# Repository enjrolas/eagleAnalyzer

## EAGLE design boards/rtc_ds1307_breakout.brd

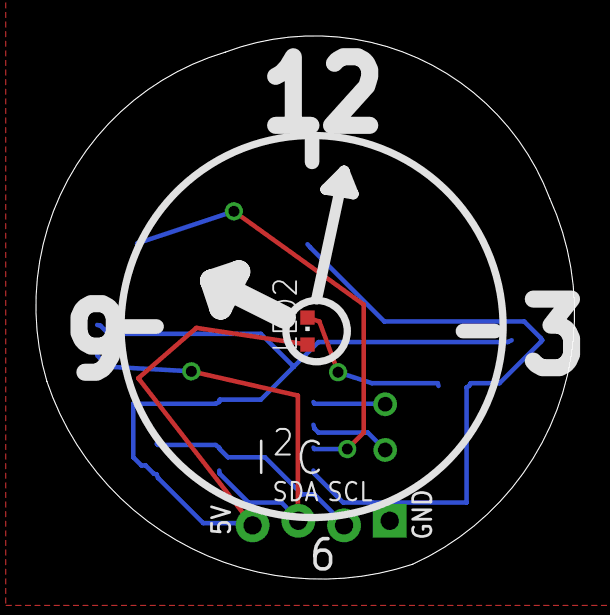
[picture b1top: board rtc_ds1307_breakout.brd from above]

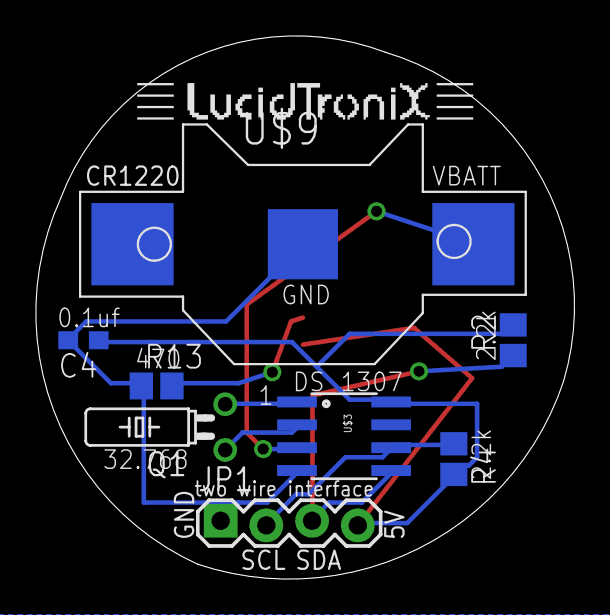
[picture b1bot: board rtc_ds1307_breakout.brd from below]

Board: 2 copper layers, 29.9 x 30.2 mm, 10 parts (9 on the bottom side), 8 nets.

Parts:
C4: 0.1uf; C0603
JP1: 1X04_LOCK
LED2: CHIPLED_0603
Q1: 32.768; TC26H
R2, R4: 2.2k; R0805
R13: 300; R0805
U$1: LUCIDTRONIX_LOGO_.75_INCH
U$3: DS1307SO8; SO08
U$9: CR1220-SMD

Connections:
+5V: C4.1, JP1.4, LED2.A, R2.2, R4.2, U$3.8
GND: C4.2, JP1.1, R13.1, U$3.4, U$9.-
unnamed: Q1.1, U$3.2
unnamed: U$3.3, U$9.+$2
unnamed: Q1.2, U$3.1
unnamed: LED2.C, R13.2
SCL: JP1.2, R4.1, U$3.6
SDA: JP1.3, R2.1, U$3.5

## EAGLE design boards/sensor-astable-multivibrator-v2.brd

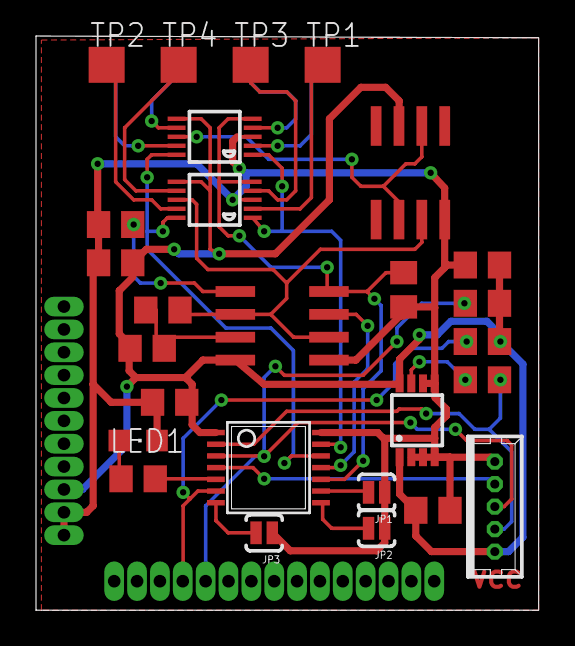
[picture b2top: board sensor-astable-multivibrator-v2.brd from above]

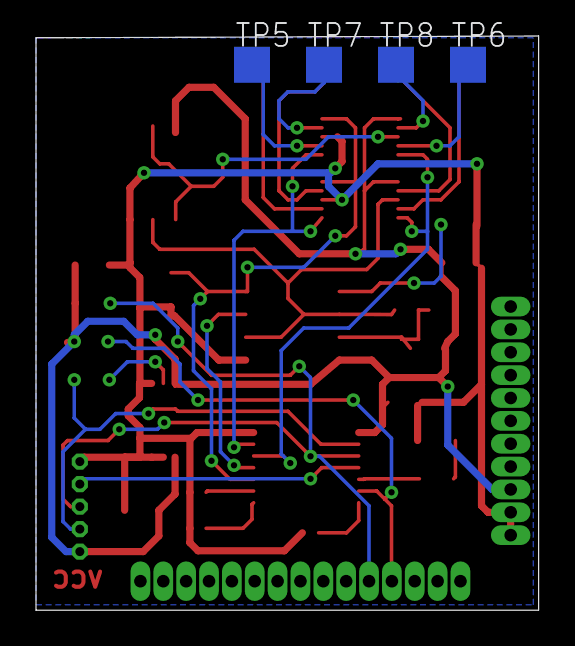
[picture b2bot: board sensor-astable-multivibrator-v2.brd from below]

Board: 2 copper layers, 27.9 x 31.9 mm, 32 parts (4 on the bottom side), 28 nets.

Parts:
C1: 100n; C0805
C3, C4, C5: 0,1µF; C0805
CT: 10u; C0805
IC1: TLC555; SO08
JP1, JP2, JP3: SJ_2S-NO
LED1: CHIPLED_0805
R1, R4, R5: 10k; R0805
R6: 22; R0805
R9: 27; R0805
RA: 100k; R0805
RB: 1k; R0805
THS4281: THS4281; SO08
TP1, TP2, TP3, TP4, TP5, TP6, TP7, TP8: TPTP20SQ; TP20SQ
U$1: CAPSENSE-BREAKOUT-I2C; JENNIC-FOOTPRINT-RB
U$2, U$5: ADG704; MSOP10
U$3: LTC6930-X.XX; MSOP8
U$4: ATTINY20; TSSOP14
X2: PROGCON; 53047-05-OCT

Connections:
(TPI)CLK: R6.2, U$4.2, X2.2
/RESET: U$4.4, X2.4
A0: U$2.1, U$4.13, U$5.1
A1: U$2.10, U$4.12, U$5.10
ADDR0: JP1.2, U$4.9
ADDR1: JP2.2, U$4.8
ADDR2: JP3.2, U$4.7
ANTENNA: IC1.2, IC1.6, RA.2, THS4281.3, U$2.8
BLUE: R9.1, U$4.5
ENABLE: IC1.4, R1.2, U$2.5, U$4.10, U$5.5
GND: C1.2, C3.2, C4.2, C5.2, CT.2, IC1.1, JP1.1, JP2.1, JP3.1, LED1.C, R1.1, THS4281.4, U$1.P$25, U$1.P$26, U$2.3, U$3.2, U$3.3, U$3.4, U$3.5, U$3.6, U$4.14, U$5.3, X2.5
GUARD: THS4281.2, THS4281.6, U$5.8
unnamed: IC1.7, RA.1, RB.2
unnamed: TP1.TP, U$2.2
unnamed: C1.1, IC1.5
unnamed: TP2.TP, U$2.9
unnamed: TP3.TP, U$2.4
unnamed: TP4.TP, U$2.7
unnamed: TP5.TP, U$5.2
unnamed: TP6.TP, U$5.9
unnamed: TP7.TP, U$5.4
unnamed: TP8.TP, U$5.7
unnamed: R6.1, U$3.7
unnamed: LED1.A, R9.2
OUT: IC1.3, U$4.11
SCL: R5.1, U$1.P$30, U$4.6
SDA/TPIDATA: R4.1, U$1.P$31, U$4.3, X2.3
VCC: C3.1, C4.1, C5.1, CT.1, IC1.8, R4.2, R5.2, RB.1, THS4281.7, U$1.P$24, U$2.6, U$3.1, U$3.8, U$4.1, U$5.6, X2.1

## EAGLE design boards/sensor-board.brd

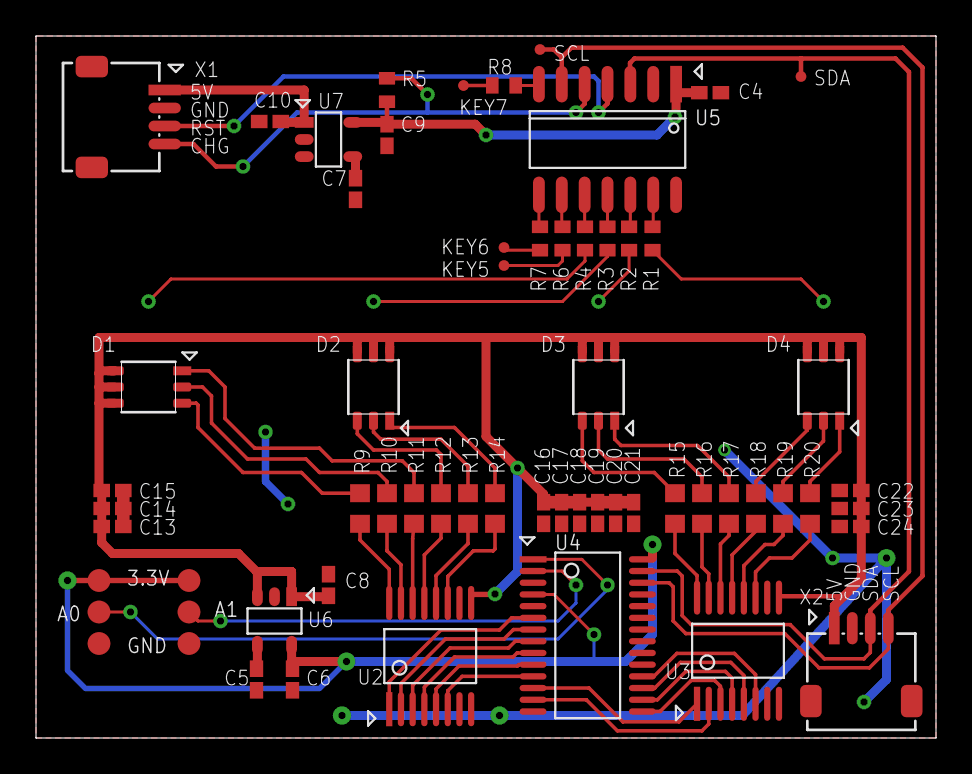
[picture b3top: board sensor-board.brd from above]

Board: 2 copper layers, 50.0 x 39.0 mm, 62 parts (0 on the bottom side), 59 nets.

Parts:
3.3V: TPB1,27; B1,27
A0, A1: TPB1,27; B1,27
C4: 0.1uF 100V; C0402K
C5, C7, C13: 0.01uF 25V; C0402K
C6, C9: 2.2uF 10V; C0402K
C8, C10: 1uF 25V; C0402K
C14, C15, C16, C17, C18, C19, C20, C21, C22, C23, C24: 0.01uF 16V; C0402K
D1, D2, D3, D4: ASMT-YTC2-0AA02; ASMT-YTC2-0AA02-REV
GND: TPB1,27; B1,27
KEY5, KEY6, KEY7: TPTP06R; TP06R
R1, R2, R3, R4, R6, R7, R8: 4.7k; R0402
R5: 47k; R0402
R9, R10, R11, R12, R13, R14, R15, R16, R17, R18, R19, R20: 60R 145mW; R0603
SCL: TPTP06R; TP06R
SDA: TPTP06R; TP06R
TP1, TP3: TPB1,27; B1,27
U2, U3: ULN2003LVPWR; TSSOP-PW-R-PDSO-G16
U4: PCA9685PW; SOT361-1
U5: AT42QT1070-SSU; SO14
U6, U7: TPS730XX; SOT23-5
X1, X2: MOLEX-501953-0407

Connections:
!CAPSENSE_CHG!: R5.1, U5.5, X1.4
!CAPSENSE_RST!: U5.4, X1.3
GND: C4.2, C5.2, C6.1, C7.2, C8.2, C9.2, C10.1, C13.1, C14.1, C15.1, C16.1, C17.1, C18.1, C19.1, C20.1, C21.1, C22.1, C23.1, C24.1, GND.TP, TP3.TP, U2.7, U2.8, U3.7, U3.8, U4.3, U4.5, U4.14, U4.23, U4.24, U4.25, U5.2, U5.14, U6.2, U7.2, X1.2, X1.5, X1.6, X2.2, X2.5, X2.6
KEY5: KEY5.TP, R6.2
KEY6: KEY6.TP, R7.2
KEY7: KEY7.TP, R8.2
LEDOUT_A1: U2.1, U4.6
LEDOUT_A2: U2.2, U4.7
LEDOUT_A3: U2.3, U4.8
LEDOUT_A4: U2.4, U4.9
LEDOUT_A5: U2.5, U4.10
LEDOUT_A6: U2.6, U4.11
LEDOUT_B1: U3.1, U4.12
LEDOUT_B2: U3.2, U4.13
LEDOUT_B3: U3.3, U4.15
LEDOUT_B4: U3.4, U4.16
LEDOUT_B5: U3.5, U4.17
LEDOUT_B6: U3.6, U4.18
unnamed: C5.1, U6.4
unnamed: A0.TP, U4.1
unnamed: A1.TP, U4.2
unnamed: C7.1, U7.4
unnamed: R6.1, U5.9
unnamed: R7.1, U5.8
unnamed: R8.1, U5.7
unnamed: R1.1, U5.13
unnamed: R2.1, U5.12
unnamed: R3.1, U5.11
unnamed: R4.1, U5.10
unnamed: D4.1, R20.2
unnamed: D1.1, R11.2
unnamed: D1.2, R10.2
unnamed: D3.3, R15.2
unnamed: D2.3, R12.2
unnamed: D2.2, R13.2
unnamed: R15.1, U3.16
unnamed: R16.1, U3.15
unnamed: D3.1, R17.2
unnamed: D3.2, R16.2
unnamed: D4.3, R18.2
unnamed: D4.2, R19.2
unnamed: R17.1, U3.14
unnamed: R18.1, U3.13
unnamed: R19.1, U3.12
unnamed: R20.1, U3.11
unnamed: D2.1, R14.2
unnamed: D1.3, R9.2
unnamed: R9.1, U2.16
unnamed: R10.1, U2.15
unnamed: R11.1, U2.14
unnamed: R12.1, U2.13
unnamed: R13.1, U2.12
unnamed: R14.1, U2.11
SCL: SCL.TP, U4.26, U5.6, X2.4
SDA: SDA.TP, U4.27, U5.3, X2.3
VDD_3_3_CAPSENSE: C4.1, C9.1, R5.2, U5.1, U7.5
VDD_3_3_PWMDRIVE: 3.3V.TP, C6.2, TP1.TP, U4.4, U4.28, U6.5
VDD_5_CAPSENSE: C10.2, U7.1, U7.3, X1.1
VDD_5_ILLUM: C8.1, C13.2, C14.2, C15.2, C16.2, C17.2, C18.2, C19.2, C20.2, C21.2, C22.2, C23.2, C24.2, D1.4, D1.5, D1.6, D2.4, D2.5, D2.6, D3.4, D3.5, D3.6, D4.4, D4.5, D4.6, U2.9, U3.9, U6.1, U6.3, X2.1

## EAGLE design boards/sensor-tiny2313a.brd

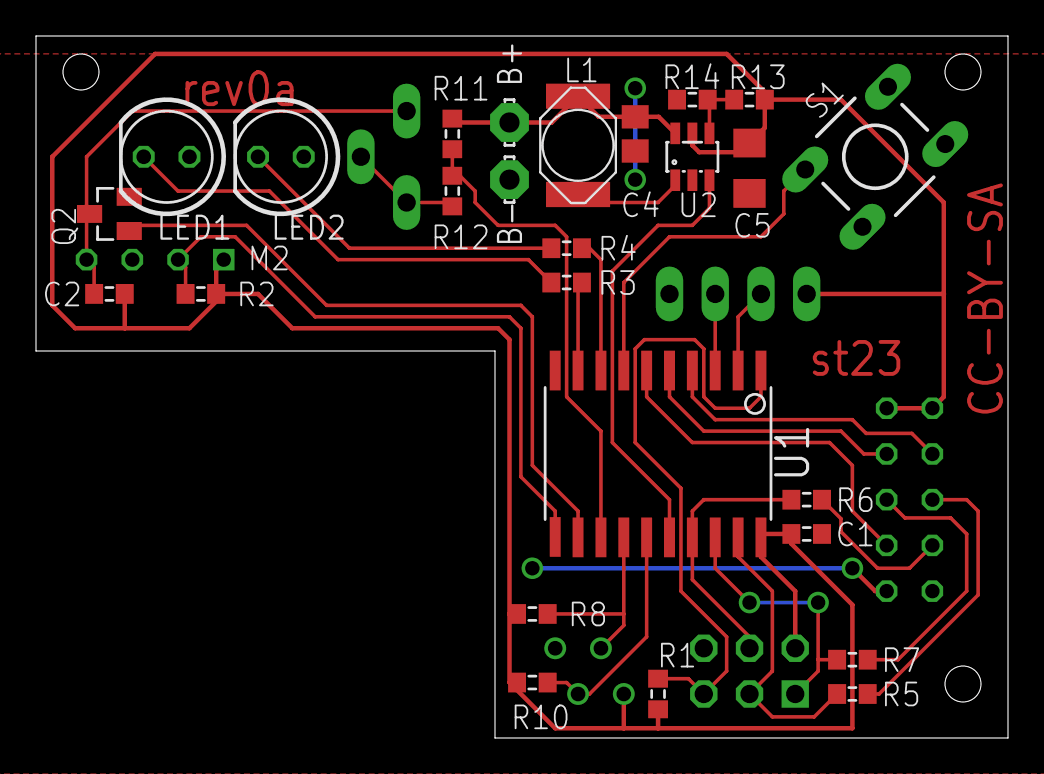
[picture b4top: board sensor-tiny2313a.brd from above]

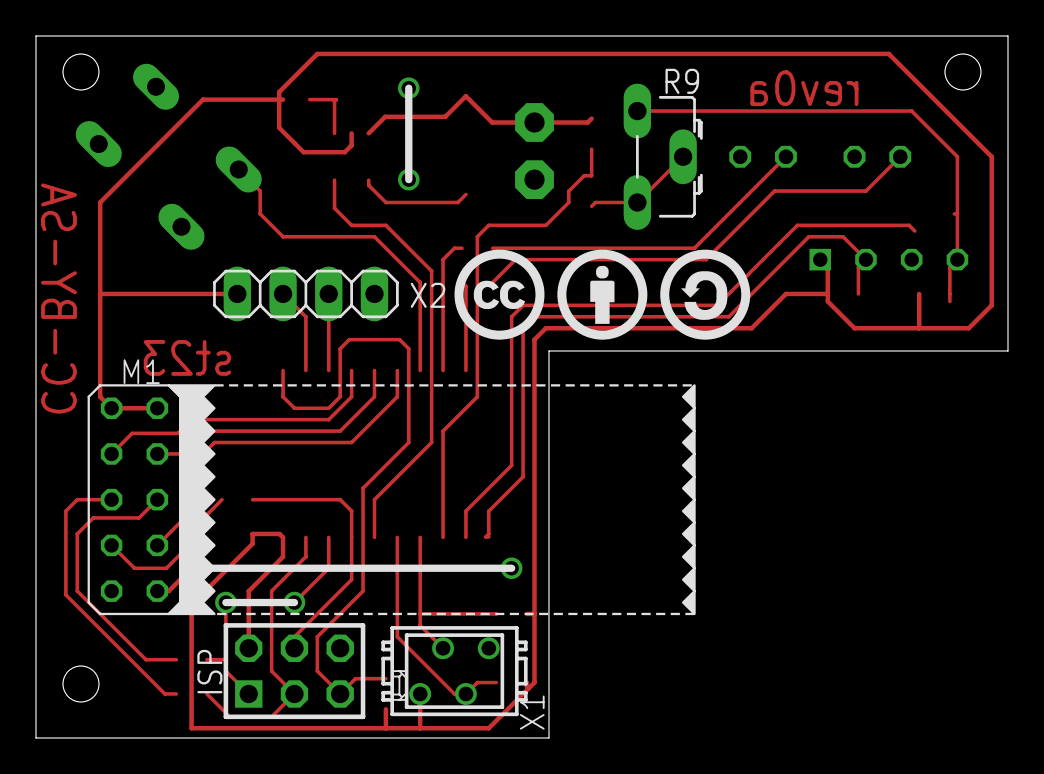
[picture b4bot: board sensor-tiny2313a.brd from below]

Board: 2 copper layers, 54.0 x 39.0 mm, 36 parts (8 on the bottom side), 30 nets.

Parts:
B+: LSP11
B-: LSP11
C1, C2: 100n; C0603
C4: 4u7; C0805
C5: 22u; C1206
ISP: ML6; AVR-ISP-6
L1: 4u7; PISG
LED1: GR LC; LED5MM
LED2: RT LC; LED5MM
M1: NRF24L01P-M; NRF24L01P-A
M2: DHT22-NP; DHT22-NOPRINT
Q2: IRLML2502; MICRO3
R1, R2, R11: 10k; R0603
R3: 470; R0603
R4: 510; R0603
R5, R6, R7, R8, R10: 4k7; R0603
R9: 2k5; CA6H
R12: 12k; R0603
R13: 470k; R0603
R14: 270k; R0603
S1: DTS-6
U1: TINY2313-*S*; SO20L$
U2: MCP1640C; SOT23-6
U$1: CC-TPLACE-HALF; CC_TPLACE_HS
U$2: SP6029TOP; SP6029T
U$3: BY-TPLACE-HS; BY_TPLACE_HS
U$4: SA-TPLACE-HALF; SA_TPLACE_HS
X1: I2C; MICROMATCH-4
X2: serial; 1X04

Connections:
!RESET: ISP.5, R1.2, U1.1
AIN1: R11.2, R12.1, U1.13
DHTON: Q2.1, U1.12
DI: ISP.4, R6.1, U1.17
DO: ISP.1, R7.2, U1.18
GND: B-.MP, C1.2, C4.2, C5.2, ISP.6, LED1.A, LED2.A, M1.GND_A, M1.GND_B, Q2.2, R14.1, S1.3, S1.4, U1.10, U2.2, X1.4, X2.4
ICP1: M2.2, R2.2, U1.11
LED1: R3.1, U1.9
LED2: R4.1, U1.8
unnamed: LED2.K, R4.2
unnamed: C2.1, M2.4, Q2.3, R9.A
unnamed: LED1.K, R3.2
unnamed: R9.E, R9.S, R12.2
unnamed: L1.1, U2.1
unnamed: R13.2, R14.2, U2.4
PWRON: U1.16, U2.3
RDI: M1.MISO, R6.2
RDO: M1.MOSI, R7.1
RFCE: M1.CE, U1.4
RFCSN: M1.CSN, U1.5
RFIRQ: M1.IRQ, U1.6
RSCK: M1.SCK, R5.2
RXD: U1.2, X2.2
SCK: ISP.3, R5.1, U1.19
SCL: R10.2, U1.15, X1.3
SDA: R8.2, U1.14, X1.2
SW1: S1.1, U1.7
TXD: U1.3, X2.3
VBAT: B+.MP, C4.1, L1.2, R11.1, U2.6
VCC: C1.1, C2.2, C5.1, ISP.2, M1.VCC_A, M1.VCC_B, M2.1, R1.1, R2.1, R8.1, R10.1, R13.1, U1.20, U2.5, X1.1, X2.1

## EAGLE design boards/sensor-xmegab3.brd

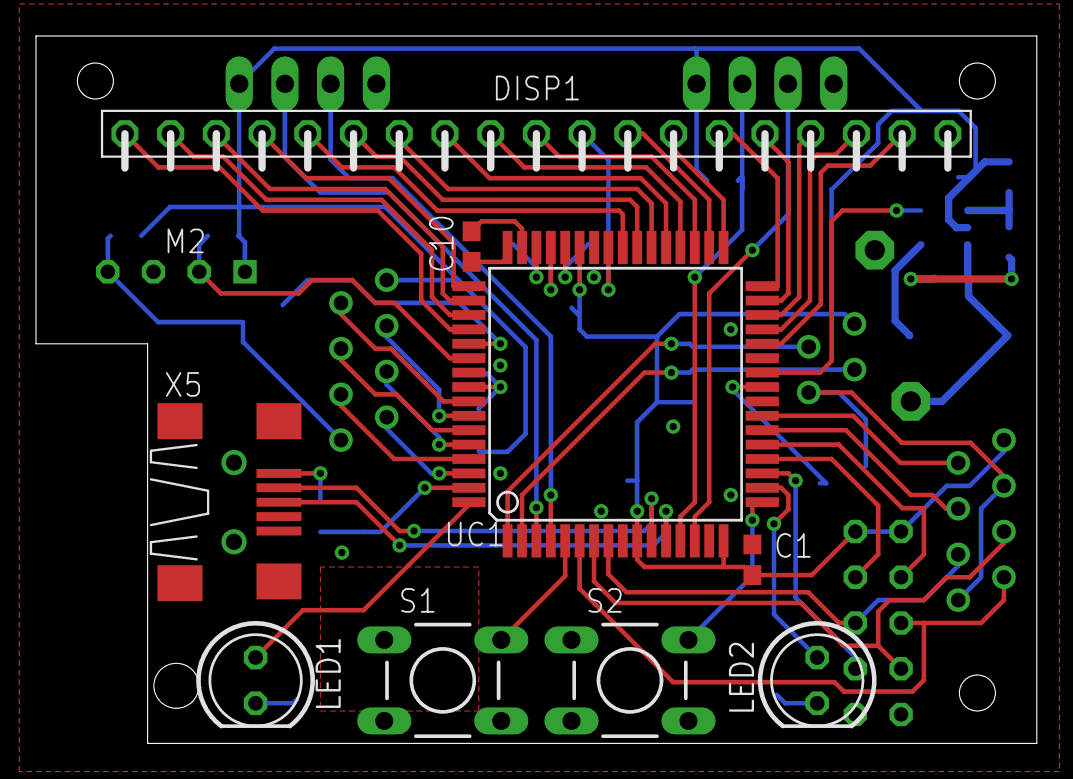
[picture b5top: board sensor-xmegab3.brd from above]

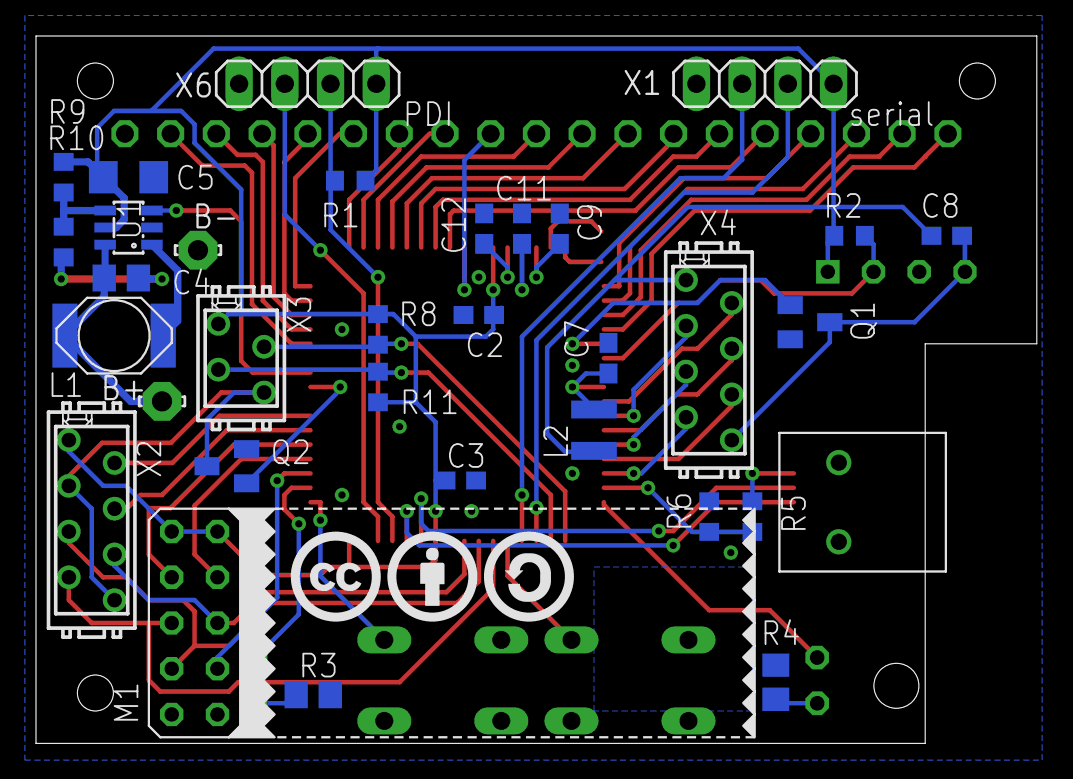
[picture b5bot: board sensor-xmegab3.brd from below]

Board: 2 copper layers, 55.6 x 39.3 mm, 46 parts (35 on the bottom side), 65 nets.

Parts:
B+: LSP11
B-: LSP11
C1, C2, C3, C7, C8, C9, C10, C11, C12: 100n; C0603
C4: 4u7; C0805
C5: 22u; C1206
DISP1: DE325
K1: SP6029TOP; SP6029T
L1: 4u7; PISG
L2: 10u; SM-NE29
LED1: GR LC; LED5MM
LED2: RT LC; LED5MM
M1: NRF24L01P-M; NRF24L01P-A
M2: DHT22-NP; DHT22-NOPRINT
Q1, Q2: IRLML2502; MICRO3
R1, R2, R6: 10k; R0603
R3: 510; R0805
R4: 470; R0805
R5: 15k; R0603
R8, R11: 4k7; R0603
R9: 470k; R0603
R10: 270k; R0603
S1, S2: DTS-6
U1: MCP1640C; SOT23-6
U$1: CC-TPLACE-HALF; CC_TPLACE_HS
U$3: BY-TPLACE-HS; BY_TPLACE_HS
U$4: SA-TPLACE-HALF; SA_TPLACE_HS
UC1: XMEGA-B3; TQFP64
X1: serial; 1X04
X2: SPI/1W; MICROMATCH-8
X3: I2C; MICROMATCH-4
X4: ADC; MICROMATCH-8
X5: USB-MB-S
X6: PDI; 1X04

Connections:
ADC0: UC1.57, X4.2
ADC1: UC1.58, X4.3
ADC2: UC1.59, X4.4
ADC3: UC1.60, X4.5
ADC4: UC1.61, X4.6
ADC5: UC1.62, X4.7
AVCC: C7.1, L2.2, UC1.56
COM0: DISP1.4, UC1.49
COM1: DISP1.3, UC1.50
COM2: DISP1.2, UC1.51
COM3: DISP1.1, UC1.52
DHTADCON: Q1.1, UC1.53
GND: B-.MP, C1.2, C2.2, C3.2, C4.2, C5.2, C7.2, C9.1, C11.1, C12.1, M1.GND_A, M1.GND_B, Q1.2, Q2.2, R3.2, R4.2, R6.1, R10.1, S1.3, S1.4, S2.3, S2.4, U1.2, UC1.9, UC1.15, UC1.42, UC1.55, X1.4, X5.GND, X6.4
ICP: M2.2, R2.1, UC1.54
LED1: LED1.A, UC1.64
LED2: LED2.A, UC1.18
MISO: M1.MISO, UC1.7, X2.5
MOSI: M1.MOSI, UC1.8, X2.6
unnamed: LED1.K, R4.1
unnamed: R5.1, X5.VBUS
unnamed: LED2.K, R3.1
unnamed: L1.1, U1.1
unnamed: R9.2, R10.2, U1.4
unnamed: C11.2, UC1.45
unnamed: C12.2, UC1.44
unnamed: Q2.3, X2.3, X2.8, X3.4
unnamed: C8.1, M2.4, Q1.3, X4.8
unnamed: C9.2, UC1.46
unnamed: C10.1, UC1.47
unnamed: C10.2, UC1.48
PDIC: R1.2, UC1.13, X6.2
PDID: UC1.14, X6.3
PWRON: U1.3, UC1.26
RFCE: M1.CE, UC1.21
RFCSN: M1.CSN, UC1.20
RFIRQ: M1.IRQ, UC1.19
RXD: UC1.3, X1.2
SCK: M1.SCK, UC1.6, X2.7
SCL: R11.2, UC1.2, X3.3
SDA: R8.2, UC1.1, X3.2
SEG0: DISP1.5, UC1.40
SEG1: DISP1.6, UC1.39
SEG2: DISP1.7, UC1.38
SEG3: DISP1.8, UC1.37
SEG4: DISP1.9, UC1.36
SEG5: DISP1.10, UC1.35
SEG6: DISP1.11, UC1.41
SEG7: DISP1.12, UC1.34
SEG8: DISP1.13, UC1.33
SEG9: DISP1.14, UC1.32
SEG10: DISP1.15, UC1.31
SEG11: DISP1.16, UC1.30
SEG12: DISP1.17, UC1.29
SEG13: DISP1.18, UC1.28
SPI1WON: Q2.1, UC1.25
SS1WA: UC1.22, X2.4
SS1WB: UC1.23, X2.2
SW1: S1.2, UC1.5
SW2: S2.2, UC1.17
TXD: UC1.4, X1.3
USBD_N: UC1.11, X5.D-
USBD_P: UC1.12, X5.D+
USBV: R5.2, R6.2, UC1.63
VBAT: B+.MP, C4.1, L1.2, U1.6
VCC: C1.1, C2.1, C3.1, C5.1, C8.2, L2.1, M1.VCC_A, M1.VCC_B, M2.1, R1.1, R2.2, R8.1, R9.1, R11.1, U1.5, UC1.10, UC1.16, UC1.43, X1.1, X2.1, X3.1, X4.1, X6.1

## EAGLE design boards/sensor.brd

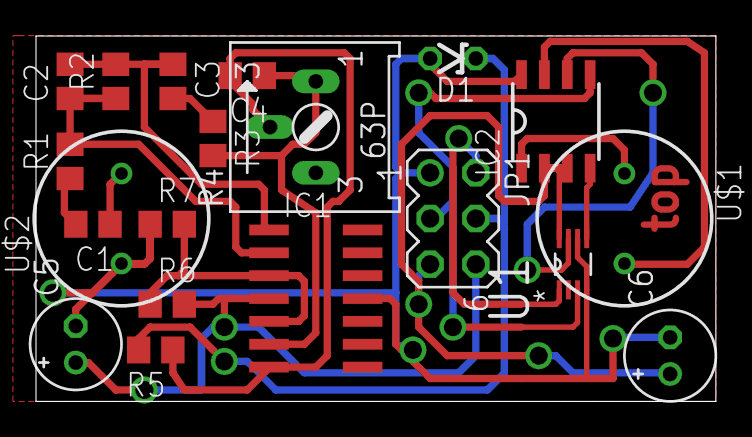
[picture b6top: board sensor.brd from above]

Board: 2 copper layers, 37.8 x 20.3 mm, 20 parts (0 on the bottom side), 18 nets.

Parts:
C1: 100n; C0805
C2, C3, C4: C0805
C5, C6: 10uF; E2-5
D1: 3V3; ZDIO-2.5
IC1: LM324D; SO14
IC2: BD6211F; SOP8
JP1: MA03-2
R1, R3: 1K5; R0805
R2: 5K6; R0805
R4: 100K; S63P
R5: 100; R0805
R6: 1K; R0805
R7: 470; R0805
U1: NC7NZ04K8X; SOP50P310X90-8N
U$1, U$2: TRANSDUCER

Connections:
GND: C5.-, C6.-, D1.A, IC1.11, IC2.8, JP1.1, R7.1, U1.4, U1.6, U$2.1
unnamed: C2.1, IC1.2, R1.2, R2.1
unnamed: C1.2, R1.1
unnamed: C2.2, C3.1, IC1.1, R2.2
unnamed: C3.2, R3.1
unnamed: C4.1, IC1.6, R3.2, R4.A
unnamed: C4.2, IC1.7, R4.S, R5.1
unnamed: C1.1, U$2.2
unnamed: IC2.1, U$1.1
unnamed: IC2.7, U$1.2
unnamed: IC2.6, U1.7
unnamed: IC2.4, U1.5
REF: IC1.3, IC1.5, R6.1, R7.2
RX: D1.C, JP1.4, R5.2
RXP: C5.+, IC1.4, JP1.6, R6.2
TX: IC2.5, JP1.3, U1.3
TXP: C6.+, IC2.2, IC2.3, JP1.5, U1.8
TX_EN: JP1.2, U1.1

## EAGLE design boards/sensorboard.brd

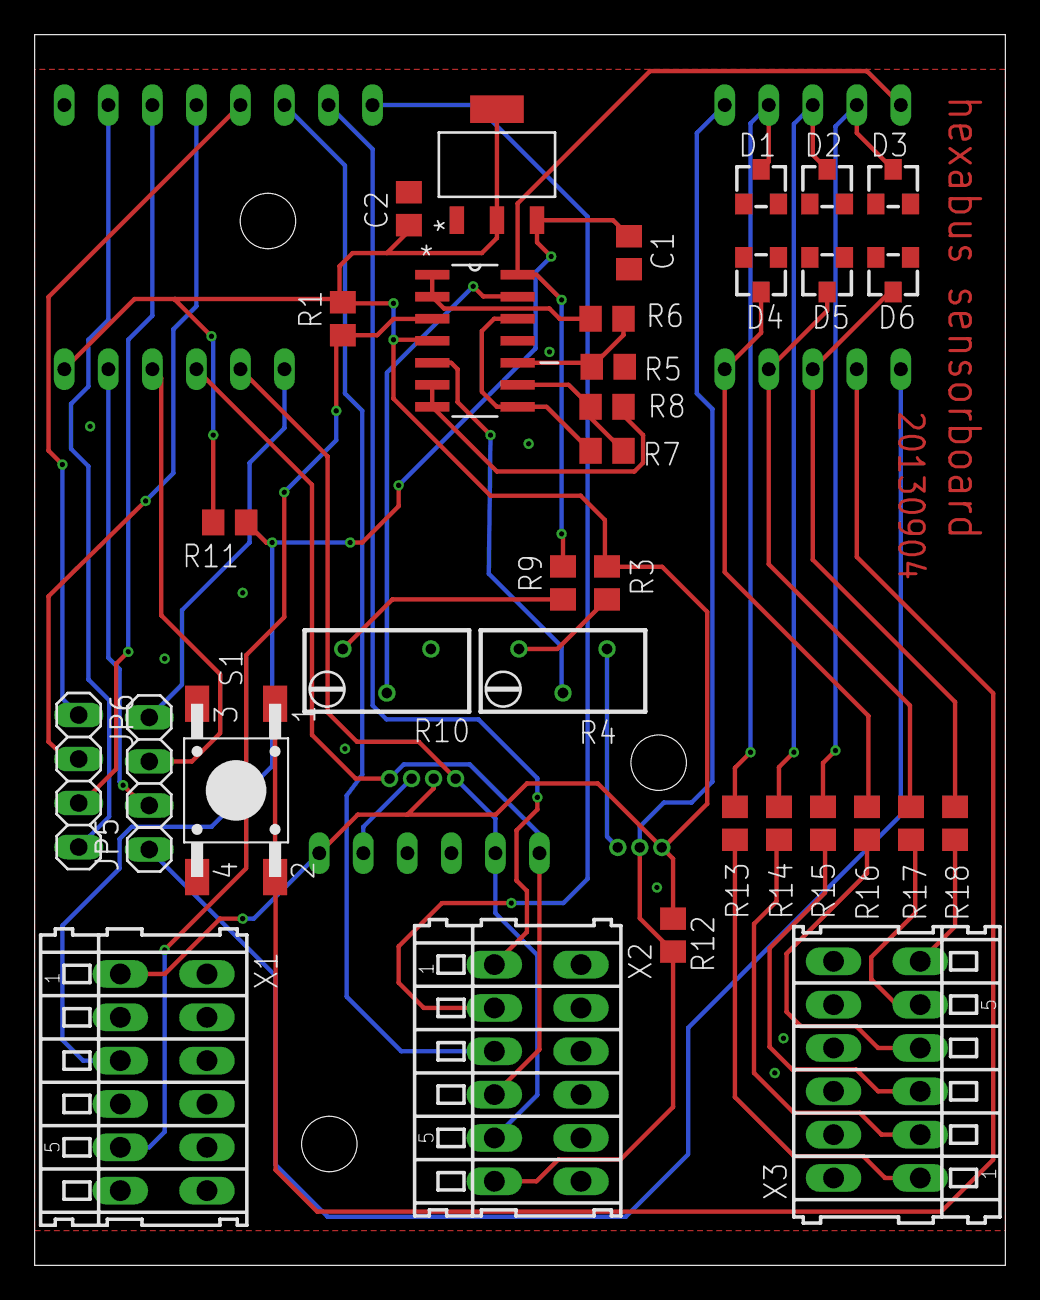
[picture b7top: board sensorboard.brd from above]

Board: 2 copper layers, 56.0 x 71.0 mm, 37 parts (0 on the bottom side), 41 nets.

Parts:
C1, C2: 10u; C0805
D1, D2, D3, D4, D5, D6: BZX84CSMD; TO236
JP5, JP6: 1X04
R1: 1k; R0805
R3: 100k; R0805
R4: 10k; RTRIMT93YB
R5, R6, R7, R8: 470k; R0805
R9: 47k; R0805
R10: 20k; RTRIMT93YB
R11: 0R; R0805
R12: 4k7; R0805
R13, R14, R15, R16, R17, R18: 330R; R0805
S1: TASTER-9314_SMD
U1: LM1117MP-3.3; SOT230P696X180-4N
U2: LM324D; SOIC127P600X175-14N
U$1: HEXABUS
U$2: HYT271-THT
U$3: BMP085; BREAKOUT
U$5: DS18S20; TO-92
X1, X2, X3: 233-206

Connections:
+3V3: C2.1, R1.2, R3.2, R11.2, R12.2, U1.2, U1.4, U2.4, U$1.VCC, U$2.VDD, U$3.VCC, U$5.VDD, X1.B1
+5V: C1.1, R11.1, U1.3, X1.B3
BTN: JP5.4, U$1.BTN
DQ: R12.1, U$1.PA0, U$5.DQ, X2.B6
GND: C1.2, C2.2, D1.A, D2.A, D3.A, D4.A, D5.A, D6.A, R4.1, R5.1, R10.1, S1.3, S1.4, U1.1, U2.11, U$1.GND, U$2.GND, U$3.GND, U$5.GND, X1.B2, X1.B4, X1.B6
GPIO1: R13.2, X3.B1
GPIO2: R14.2, X3.B2
GPIO3: R15.2, X3.B3
GPIO4: R16.2, X3.B4
GPIO5: R17.2, X3.B5
GPIO6: R18.2, X3.B6
IO1: D1.C, R13.1, U$1.PA1
IO2: D2.C, R14.1, U$1.PA2
IO3: D3.C, R15.1, U$1.PA3
IO4: D4.C, R16.1, U$1.PA5
IO5: D5.C, R17.1, U$1.PA6
IO6: D6.C, R18.1, U$1.PA7
MISO: U$1.MISO, X2.B1
MOSI: U$1.MOSI, X2.B2
unnamed: R6.1, U2.1, U2.2
unnamed: R7.1, U2.6, U2.7
unnamed: R5.2, R6.2, U2.10
unnamed: R7.2, R8.2, U2.9
unnamed: R10.2, U2.13
unnamed: R9.1, R10.3
unnamed: R3.1, R4.3
OFFSET: R4.2, U2.5
PB0: JP6.1, U$1.PB0
PB1: JP6.2, U$1.PB1
PB2: JP6.3, U$1.PB2
PB3: JP6.4, U$1.PB3
PC7: JP5.1, U$1.PC7
PD3: JP5.2, U$1.PD3
PD4: JP5.3, U$1.PD4
PT100: R1.1, U2.3, X1.B5
S1: S1.1, S1.2, U$1.PC6
SCL: U$1.SCL, U$2.SCL, U$3.SCL, X2.B5
SCLK: U$1.SCLK, X2.B3
SDA: U$1.SDA, U$2.SDA, U$3.SDA, X2.B4
TEMPERATURE: R9.2, U2.14, U$1.PA4
U_M: R8.1, U2.8, U2.12

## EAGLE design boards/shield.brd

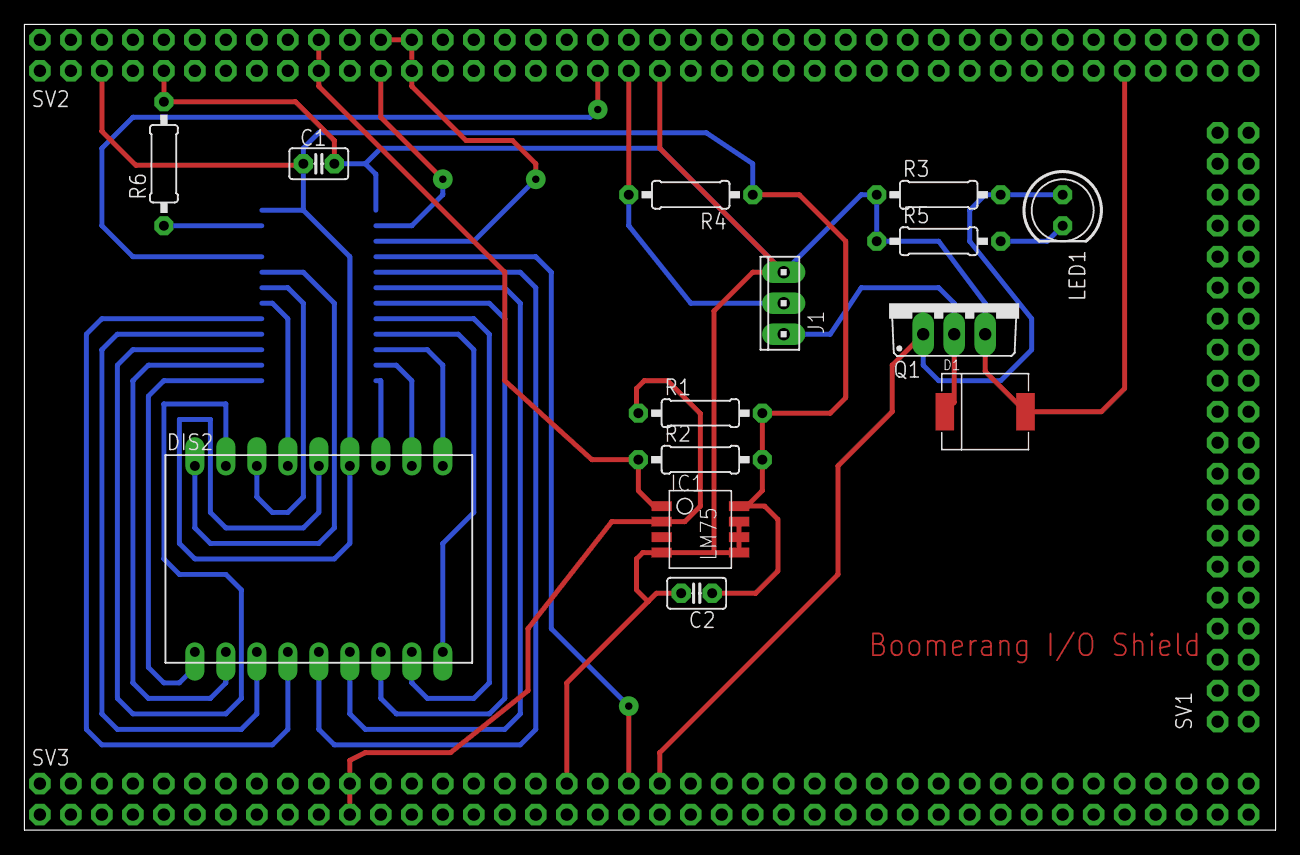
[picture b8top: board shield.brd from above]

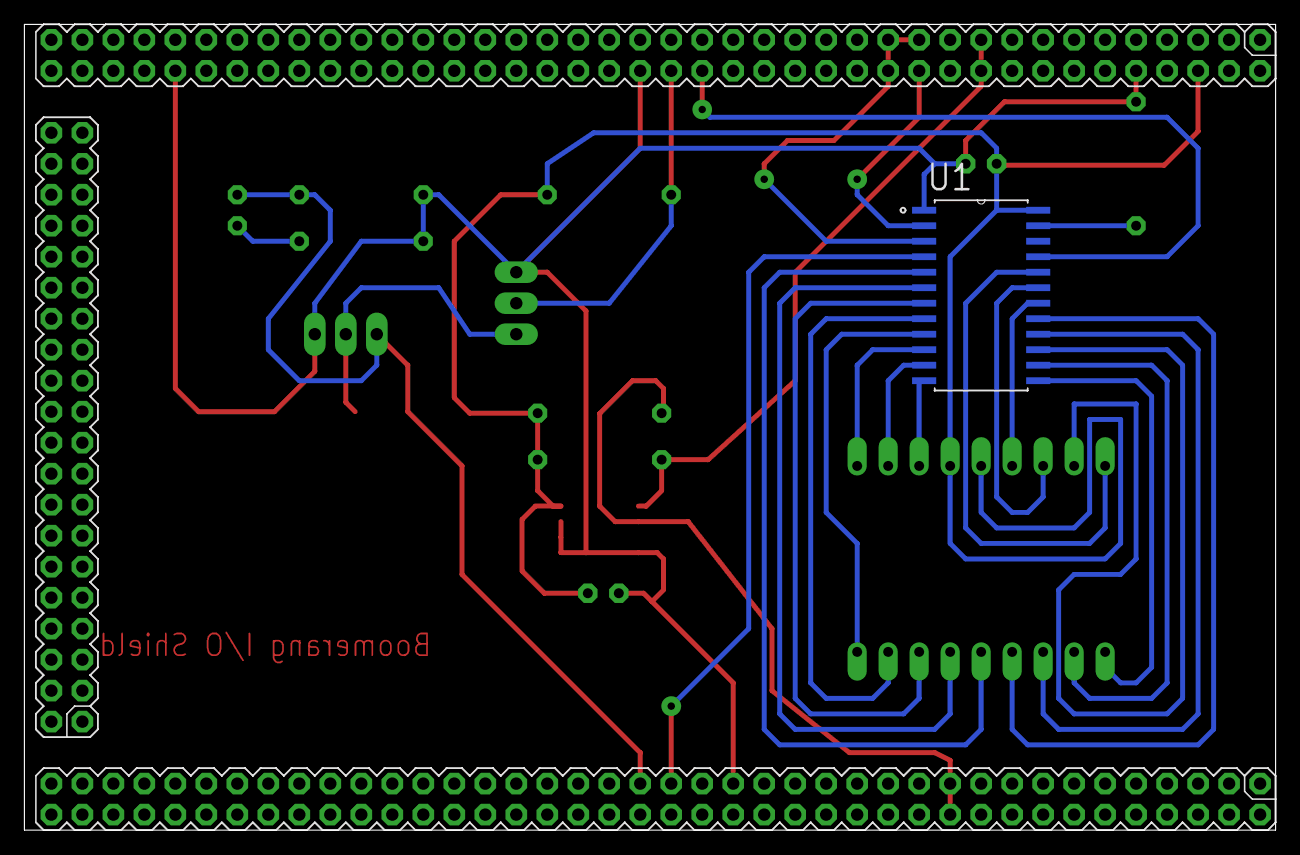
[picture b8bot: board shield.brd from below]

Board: 2 copper layers, 102.5 x 66.0 mm, 18 parts (4 on the bottom side), 29 nets.

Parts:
C1, C2: 100n; C2.5-2
D1: 1.5SMCJ33A; DO214AB
DIS2: HDSP-521E; HDSP-R
IC1: LM75; SO8_LM75
J1: 10X03MTA
LED1: LED5MM
Q1: IPP114N03L; TO220BV
R1, R2, R3, R4: 10k; 0207/10
R5: 330; 0207/10
R6: 330R; 0207/10
SV1: MA20-2
SV2, SV3: MA40-2
U1: TLC5925IDWR; SOIC127P1030X265-24N

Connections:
+3V3: C1.1, C2.1, DIS2.13, DIS2.14, IC1.8, R1.2, R2.2, R4.1, SV2.6, U1.24
GND: C1.2, C2.2, D1.A, IC1.4, IC1.5, IC1.6, IC1.7, J1.1, Q1.S, R3.1, R5.1, R6.2, SV2.10, SV2.42, SV2.72, SV3.35, U1.1
unnamed: DIS2.5, U1.5
unnamed: DIS2.6, U1.6
unnamed: DIS2.7, U1.7
unnamed: DIS2.8, U1.8
unnamed: DIS2.9, U1.9
unnamed: DIS2.10, U1.10
unnamed: DIS2.11, U1.11
unnamed: DIS2.12, U1.12
unnamed: DIS2.1, U1.13
unnamed: DIS2.2, U1.14
unnamed: DIS2.17, U1.15
unnamed: DIS2.3, U1.16
unnamed: DIS2.4, U1.17
unnamed: DIS2.15, U1.18
unnamed: DIS2.16, U1.19
unnamed: DIS2.18, U1.20
unnamed: D1.K, J1.3, Q1.D
unnamed: LED1.K, R5.2
unnamed: R6.1, U1.23
P40: IC1.1, R2.1, SV2.19
P41: IC1.2, R1.1, SV3.22
P46: SV2.24, U1.2
P48: SV2.23, U1.3
P74: SV2.38, U1.21
P78: J1.2, R4.2, SV2.40
P79: SV3.39, U1.4
P83: LED1.A, Q1.G, R3.2, SV3.41

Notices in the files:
boards/sensor-tiny2313a.brd:
CC-BY-SA
parts and their libraries:
SparkFun: Licensing: CC v3.0 Share-Alike You are welcome to use this library for commercial purposes.
